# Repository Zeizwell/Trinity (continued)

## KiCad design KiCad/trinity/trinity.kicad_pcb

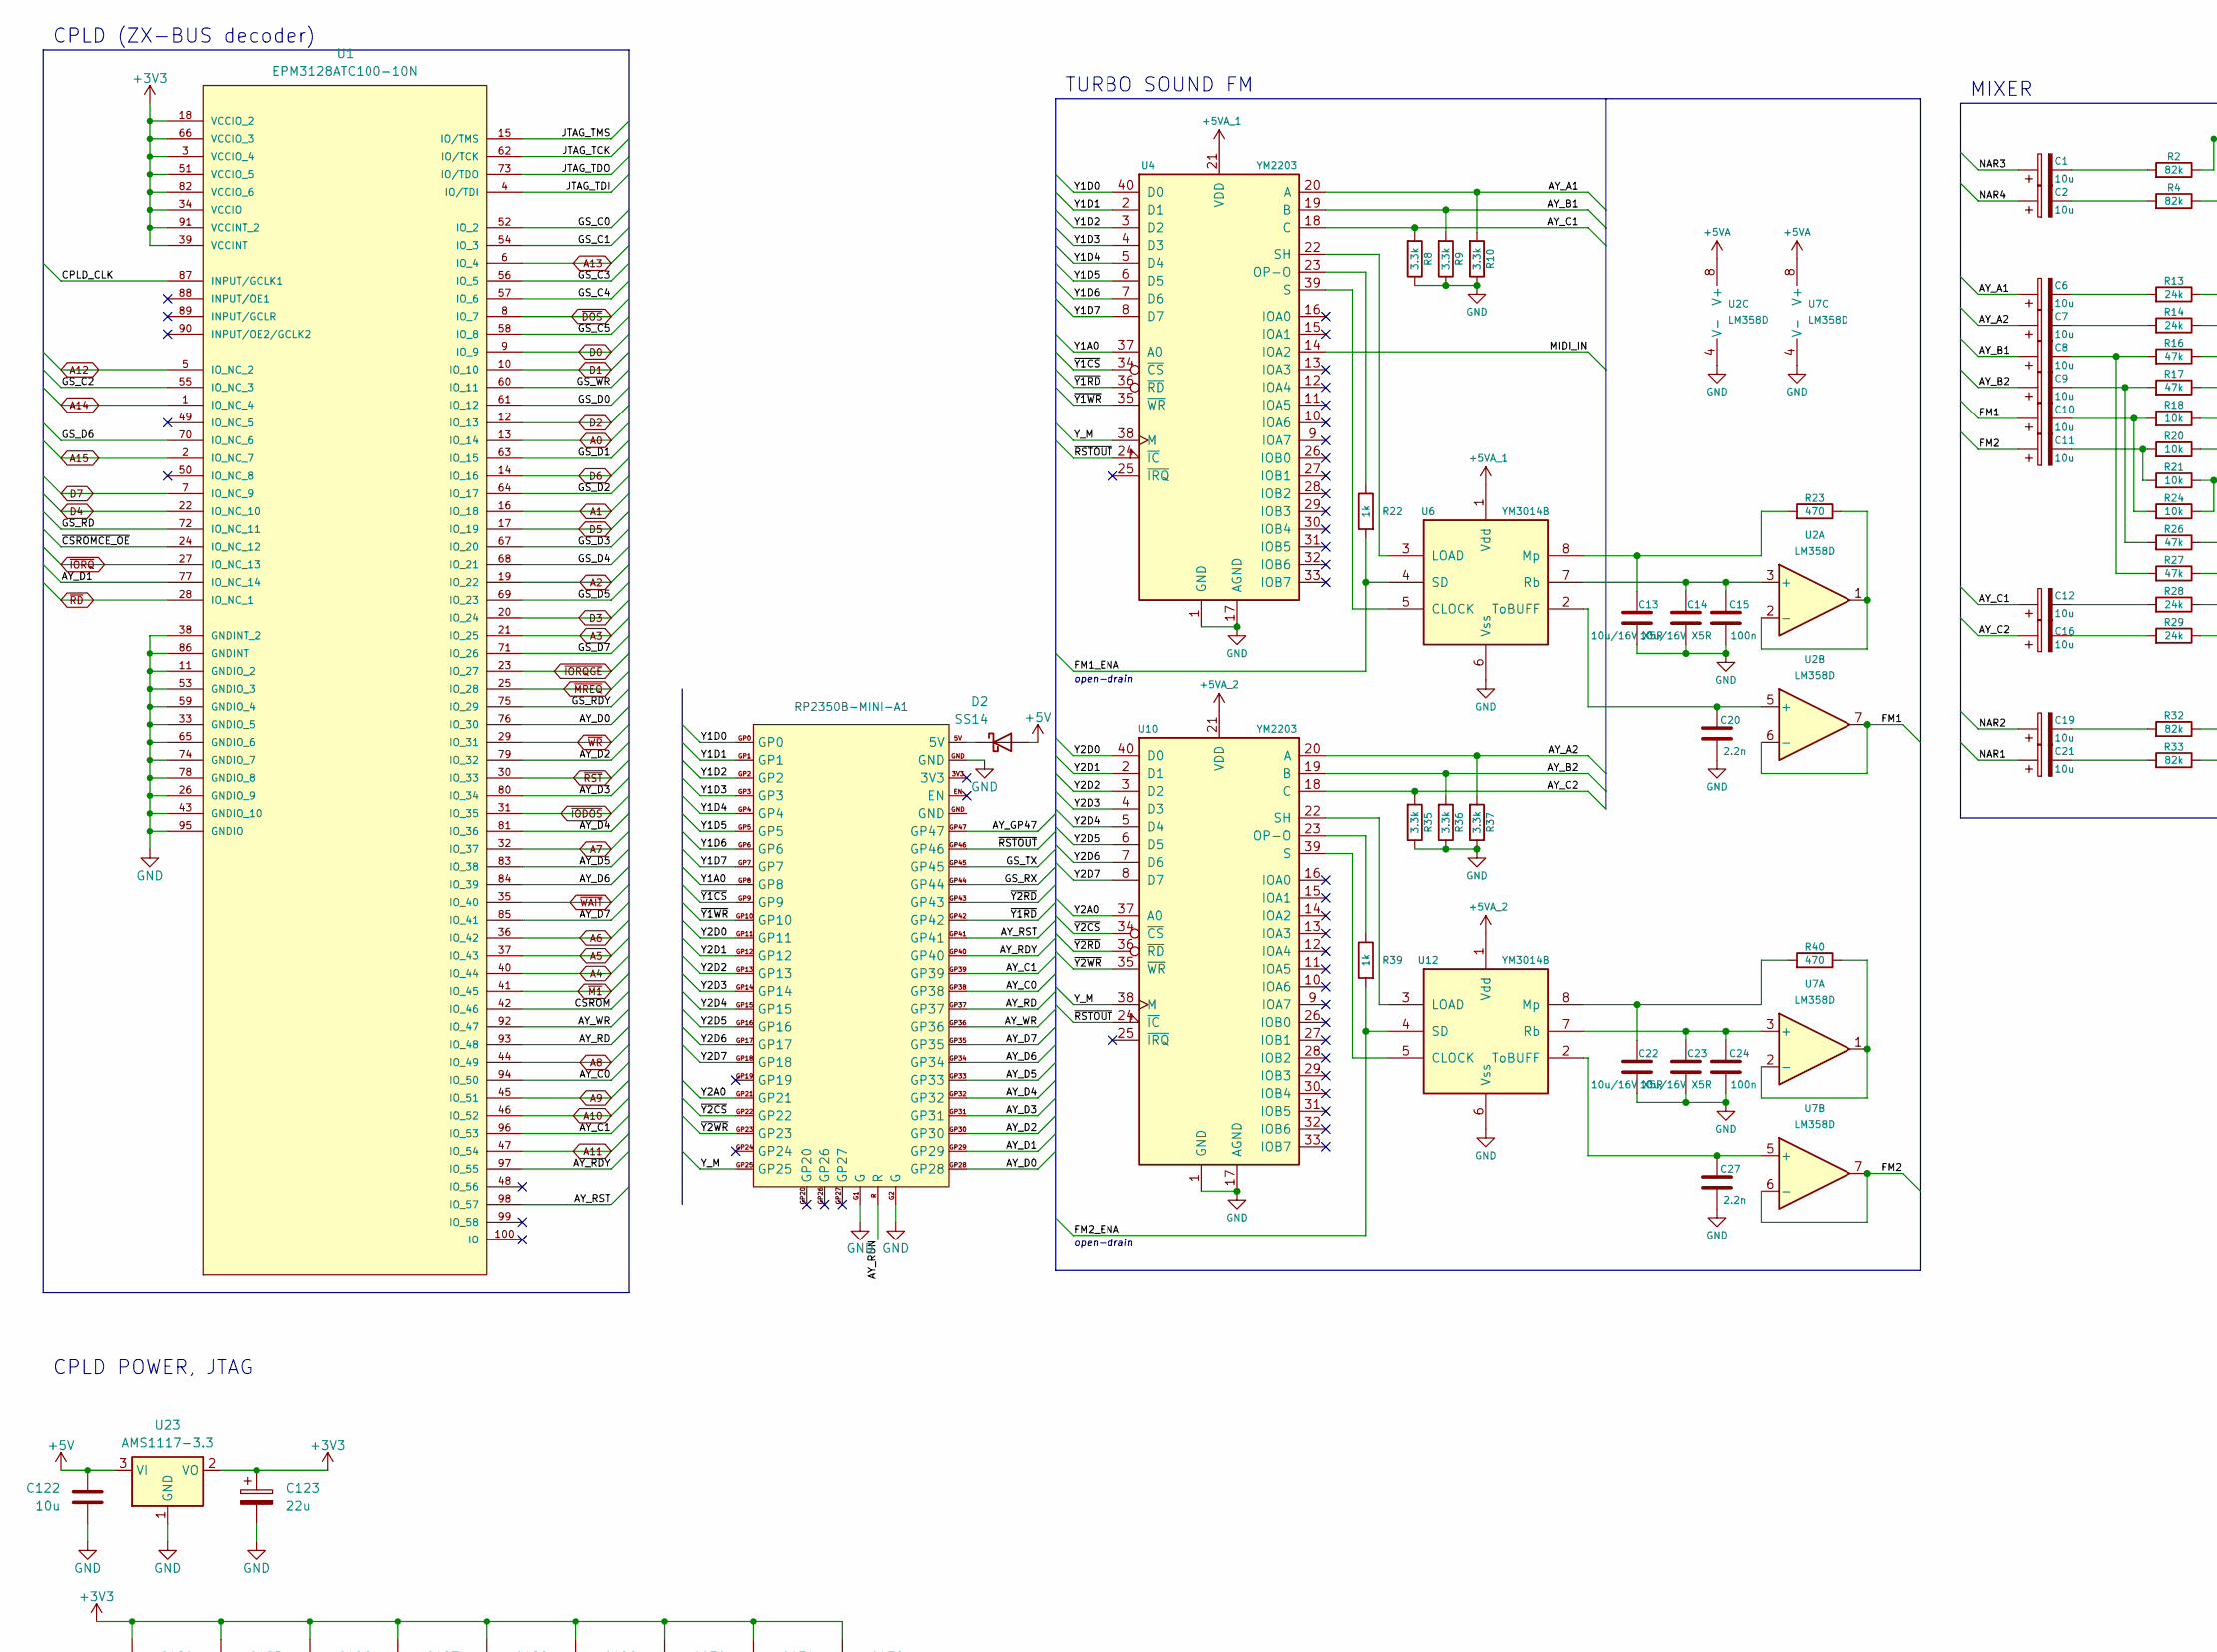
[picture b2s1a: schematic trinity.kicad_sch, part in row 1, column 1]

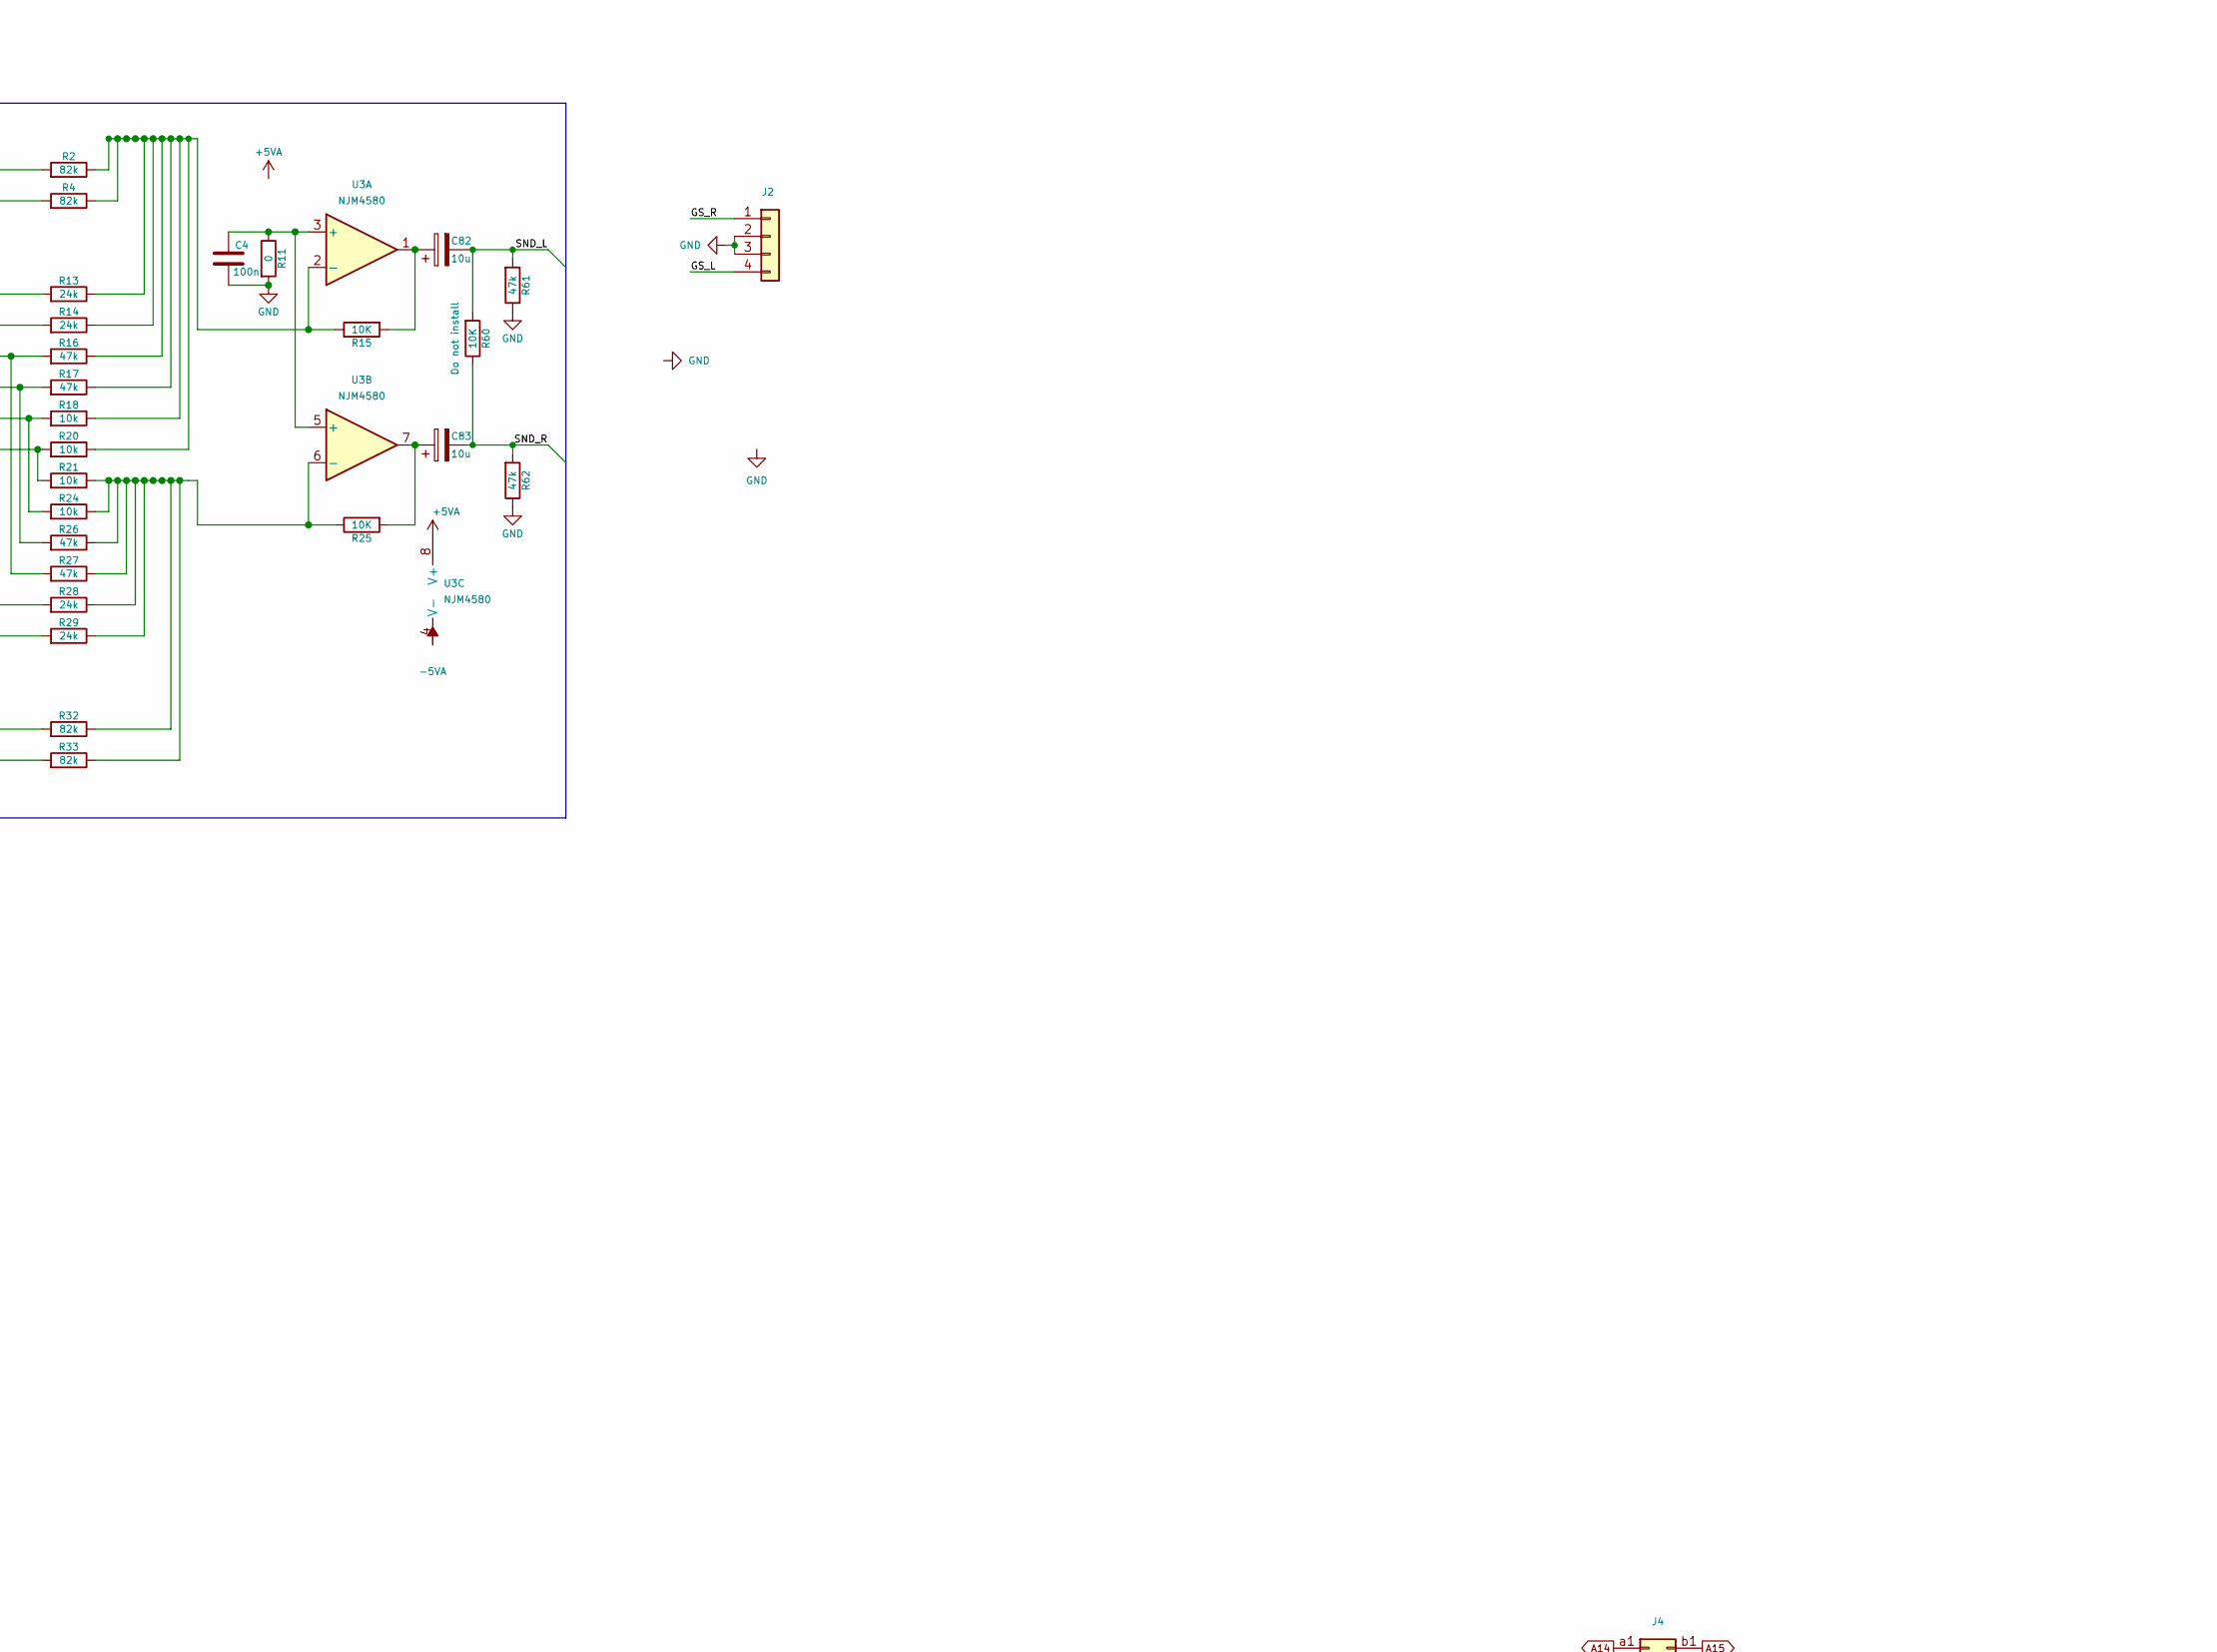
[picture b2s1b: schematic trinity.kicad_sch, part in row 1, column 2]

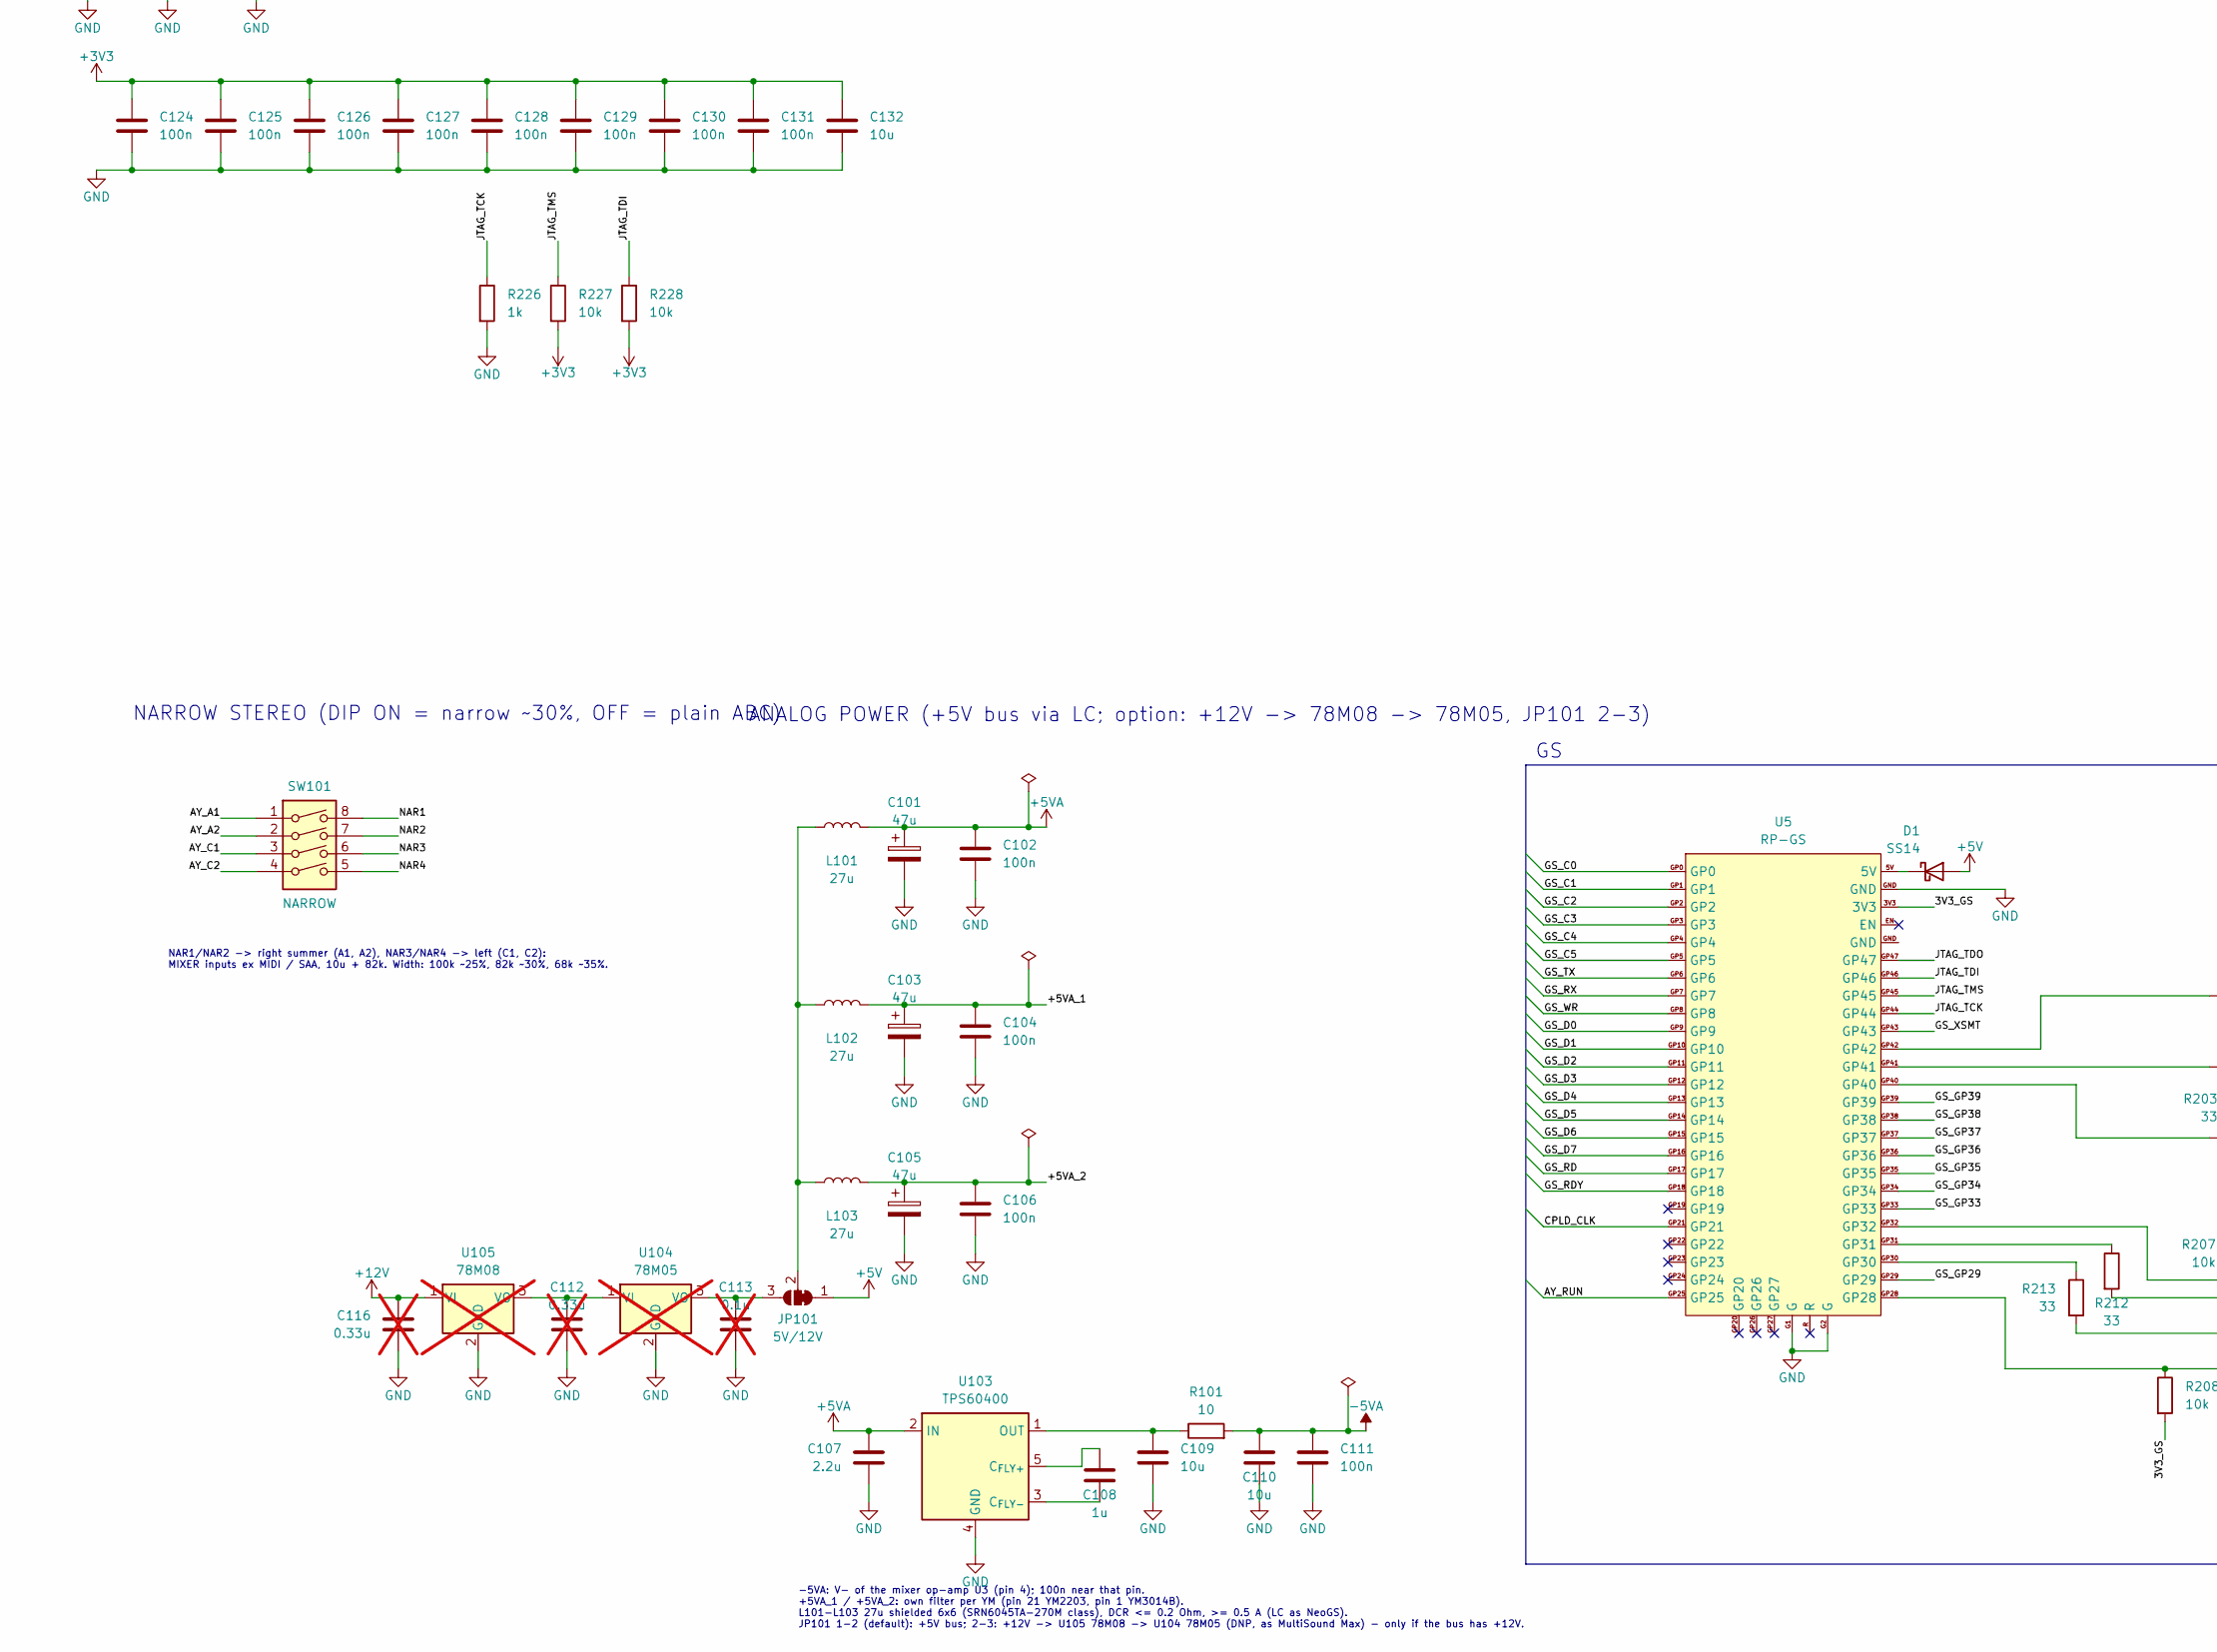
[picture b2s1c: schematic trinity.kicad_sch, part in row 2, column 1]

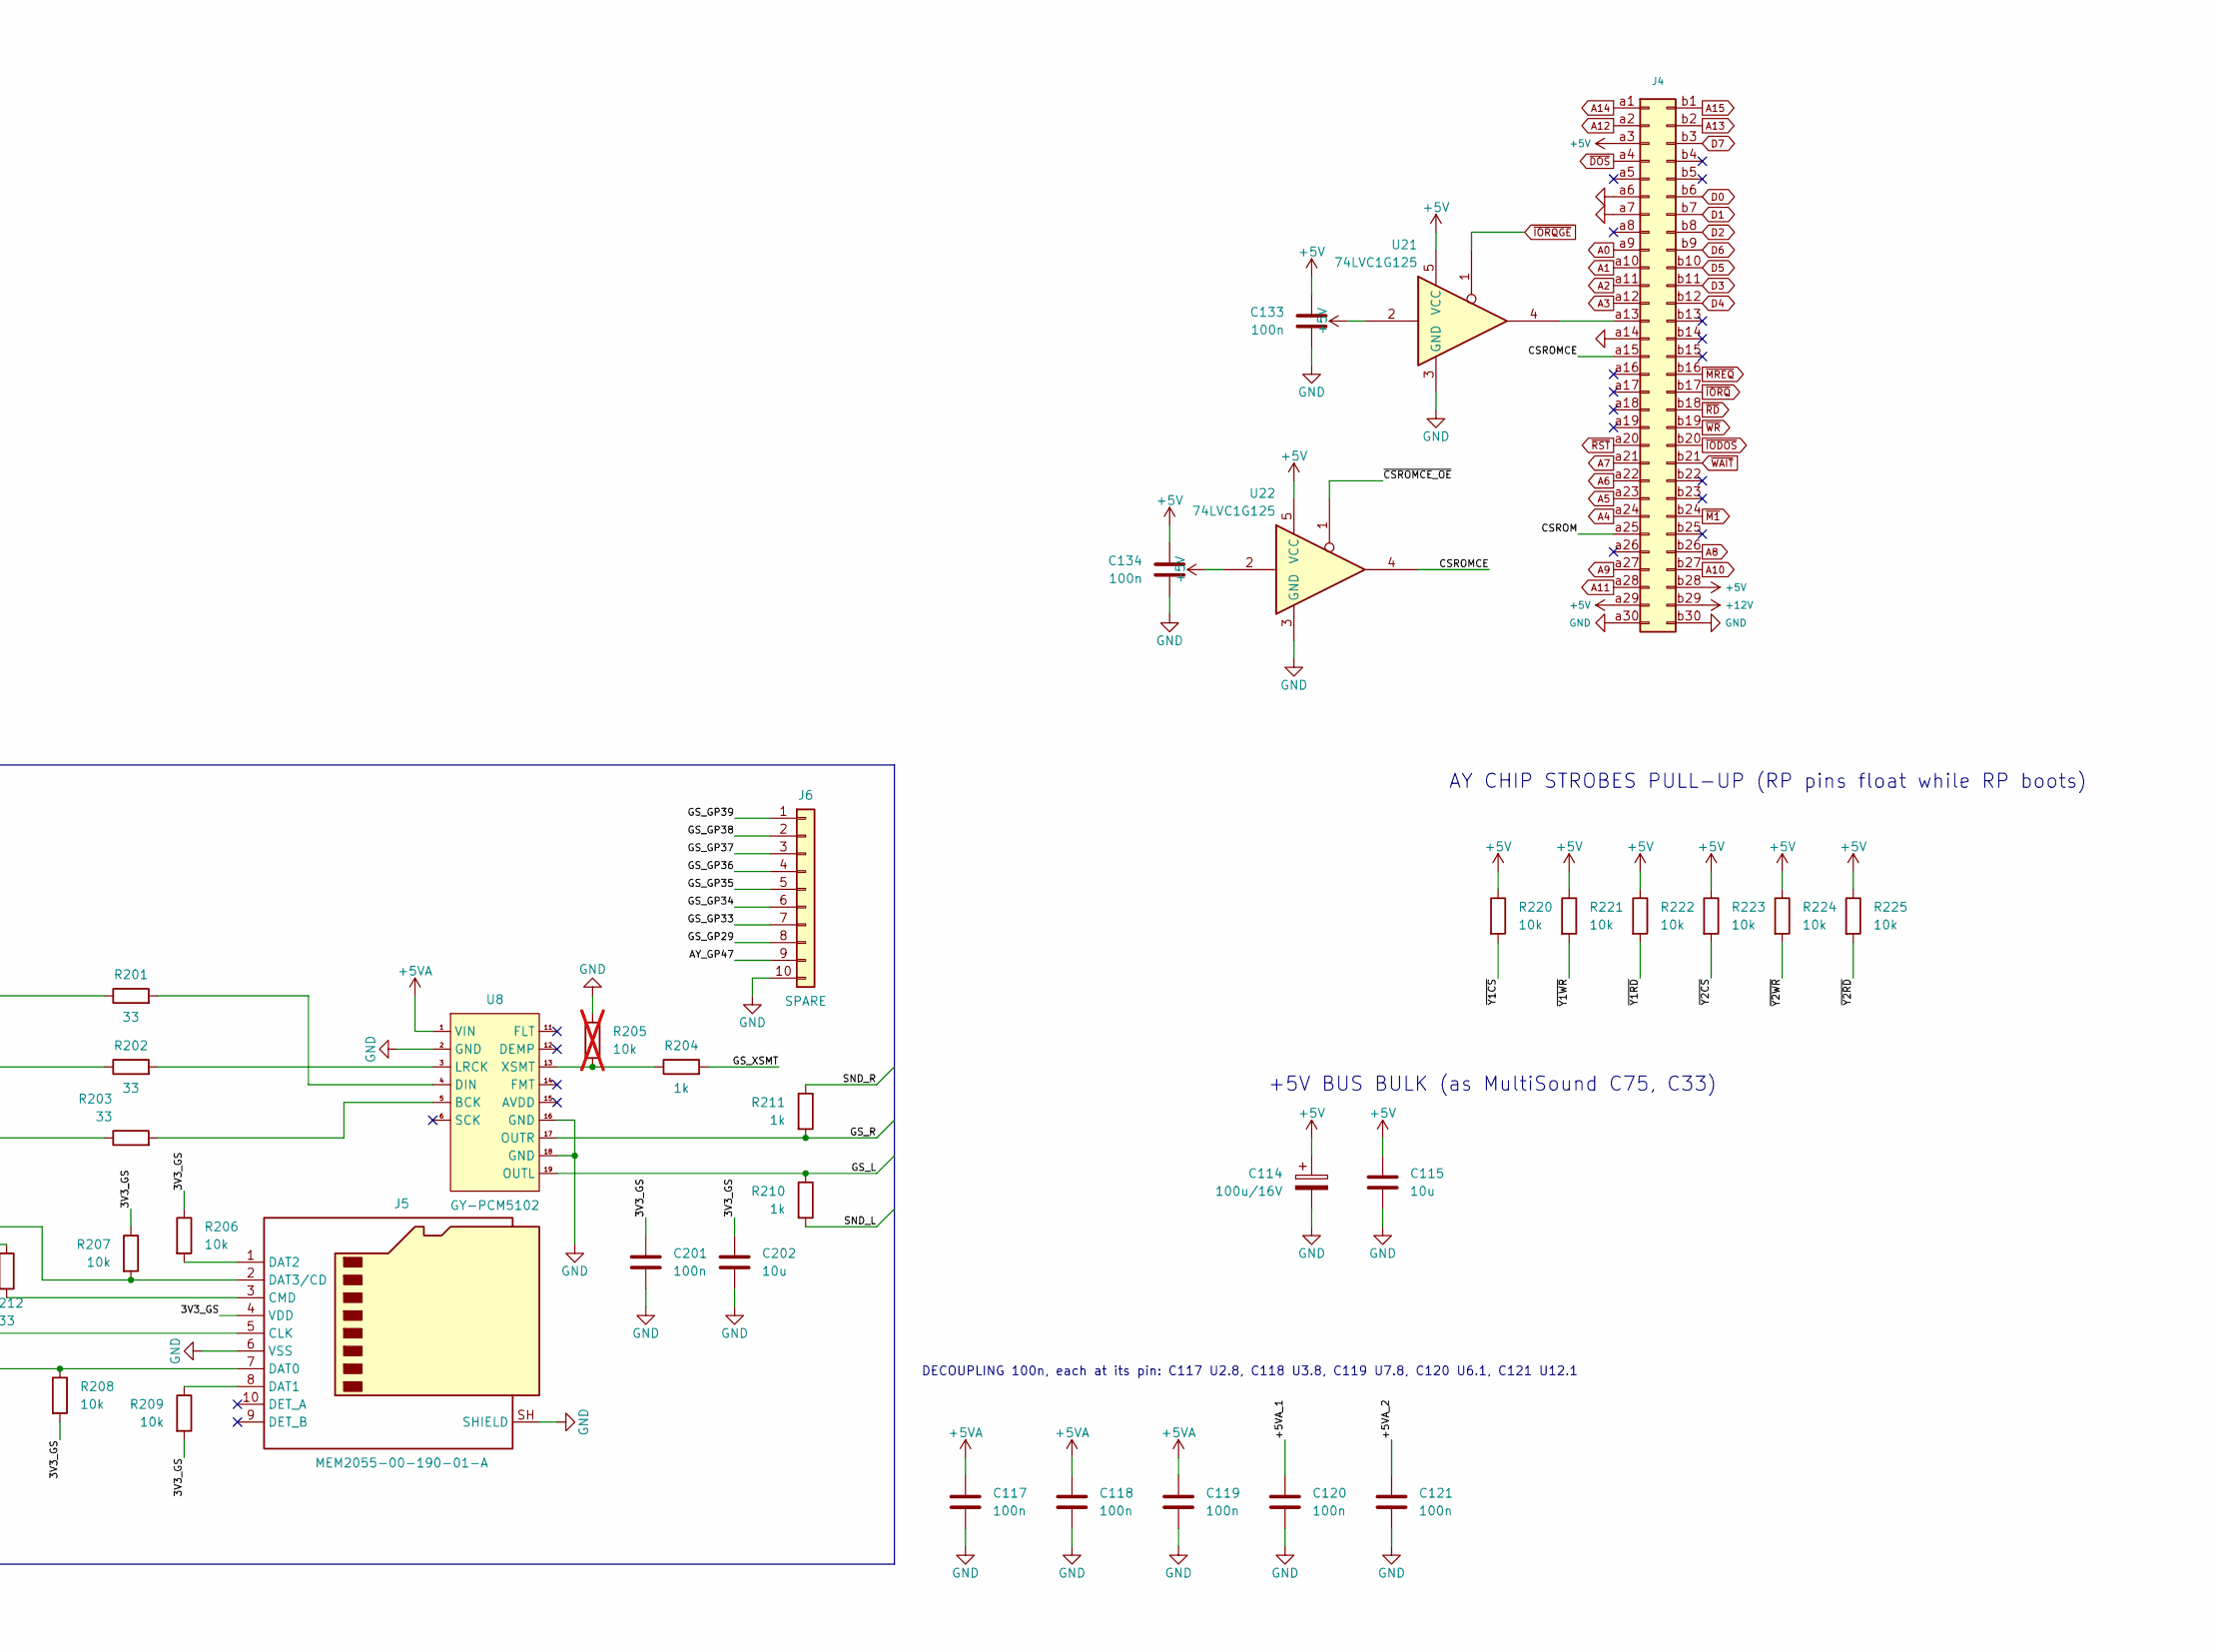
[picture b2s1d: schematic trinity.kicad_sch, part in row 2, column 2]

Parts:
C1, C2, C6, C7, C8, C9, C10, C11, C12, C16, C19, C21, C82, C83: 10u; CP_Elec_4x5.4
C4, C15, C24: 100n; C_0805_2012Metric_Pad1.18x1.45mm_HandSolder
C13, C14, C22, C23: 10u/16V X5R; C_1206_3216Metric
C20, C27: 2.2n; C_0805_2012Metric_Pad1.18x1.45mm_HandSolder
C101, C103, C105: 47u; CP_Elec_5x5.4
C102, C104, C106, C111, C117, C118, C119, C120, C121, C124, C125, C126, C127, C128, C129, C130, C131, C133, C134, C201: 100n; C_0603_1608Metric
C107: 2.2u; C_0603_1608Metric
C108: 1u; C_0603_1608Metric
C109, C110, C115, C122, C132, C202: 10u; C_0805_2012Metric
C112, C116: 0.33u; C_0603_1608Metric; not fitted
C113: 0.1u; C_0603_1608Metric; not fitted
C114: 100u/16V; CP_Elec_6.3x7.7
C123: 22u; CP_Elec_4x5.4
D1, D2: SS14; D_SMA
J2: Conn_01x04; PinHeader_1x04_P2.54mm_Vertical
J4: Conn_02x31_Row_Letter_First; ZX_NEMO_60_EDGE
J5: MEM2055-00-190-01-A; GCT-MEM2055-00-190-01-A
J6: SPARE; PinHeader_1x10_P2.54mm_Vertical
JP101: 5V/12V; SolderJumper-3_P1.3mm_Bridged12_RoundedPad1.0x1.5mm
L101, L102, L103: 27u; L_Bourns_SRN6045TA
R2, R4, R32, R33: 82k; R_0805_2012Metric_Pad1.20x1.40mm_HandSolder
R8, R9, R10, R35, R36, R37: 3.3k; R_0805_2012Metric_Pad1.20x1.40mm_HandSolder
R11: 0; R_0805_2012Metric_Pad1.20x1.40mm_HandSolder
R13, R14, R28, R29: 24k; R_0805_2012Metric_Pad1.20x1.40mm_HandSolder
R15, R25, R60: 10K; R_0805_2012Metric_Pad1.20x1.40mm_HandSolder
R16, R17, R26, R27, R61, R62: 47k; R_0805_2012Metric_Pad1.20x1.40mm_HandSolder
R18, R20, R21, R24: 10k; R_0805_2012Metric_Pad1.20x1.40mm_HandSolder
R22, R39: 1k; R_0805_2012Metric_Pad1.20x1.40mm_HandSolder
R23, R40: 470; R_0805_2012Metric_Pad1.20x1.40mm_HandSolder
R101: 10; R_0603_1608Metric
R201, R202, R203, R212, R213: 33; R_0603_1608Metric
R204, R210, R211, R226: 1k; R_0603_1608Metric
R205: 10k; R_0603_1608Metric; not fitted
R206, R207, R208, R209, R220, R221, R222, R223, R224, R225, R227, R228: 10k; R_0603_1608Metric
RP2350B-MINI-A1: rp2350b
SW101: NARROW; SW_DIP_SPSTx04_Slide_Omron_A6H-4101_W6.15mm_P1.27mm
U1: EPM3128ATC100-10N; QFP50P1600X1600X120-100N
U2, U7: LM358D; SOIC-8_3.9x4.9mm_P1.27mm
U3: NJM4580; SOIC-8_3.9x4.9mm_P1.27mm
U4, U10: YM2203; DIP-40_W15.24mm_Socket
U5: RP-GS; rp2350b
U6, U12: YM3014B; DIP-8_W7.62mm_Socket
U8: GY-PCM5102; PCM5102
U21, U22: 74LVC1G125; SOT-23-5
U23: AMS1117-3.3; SOT-223-3_TabPin2
U103: TPS60400; SOT-23-5
U104: 78M05; TO-252-2; not fitted
U105: 78M08; TO-252-2; not fitted

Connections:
+3V3: C123.1, C124.1, C125.1, C126.1, C127.1, C128.1, C129.1, C130.1, C131.1, C132.1, R227.2, R228.2, U1.3 (VCCIO_4), U1.18 (VCCIO_2), U1.34 (VCCIO), U1.39 (VCCINT), U1.51 (VCCIO_5), U1.66 (VCCIO_3), U1.82 (VCCIO_6), U1.91 (VCCINT_2), U23.2 (VO)
+5V: C114.1, C115.1, C122.1, C133.1, C134.1, D1.2 (A), D2.2 (A), J4.a3, J4.a29, J4.b28, JP101.1 (A), R220.1, R221.1, R222.1, R223.1, R224.1, R225.1, U21.2, U21.5 (VCC), U22.2, U22.5 (VCC), U23.3 (VI)
+12V: C116.1, J4.b29, U105.1 (VI)
/3V3_GS: C201.1, C202.1, J5.4 (VDD), R206.1, R207.1, R208.2, R209.2, U5.3V3
/AY_A1: C6.1, R10.2, SW101.1, U4.20 (A)
/AY_A2: C7.1, R37.2, SW101.2, U10.20 (A)
/AY_B1: C8.1, R9.2, U4.19 (B)
/AY_B2: C9.1, R36.2, U10.19 (B)
/AY_C0: RP2350B-MINI-A1.GP38, U1.94 (IO_50)
/AY_C1: C12.1, R8.2, RP2350B-MINI-A1.GP39, SW101.3, U1.96 (IO_53), U4.18 (C)
/AY_C2: C16.1, R35.2, SW101.4, U10.18 (C)
/AY_D0: RP2350B-MINI-A1.GP28, U1.76 (IO_30)
/AY_D1: RP2350B-MINI-A1.GP29, U1.77 (IO_NC_14)
/AY_D2: RP2350B-MINI-A1.GP30, U1.79 (IO_32)
/AY_D3: RP2350B-MINI-A1.GP31, U1.80 (IO_34)
/AY_D4: RP2350B-MINI-A1.GP32, U1.81 (IO_36)
/AY_D5: RP2350B-MINI-A1.GP33, U1.83 (IO_38)
/AY_D6: RP2350B-MINI-A1.GP34, U1.84 (IO_39)
/AY_D7: RP2350B-MINI-A1.GP35, U1.85 (IO_41)
/AY_GP47: J6.9, RP2350B-MINI-A1.GP47
/AY_RD: RP2350B-MINI-A1.GP37, U1.93 (IO_48)
/AY_RDY: RP2350B-MINI-A1.GP40, U1.97 (IO_55)
/AY_RST: RP2350B-MINI-A1.GP41, U1.98 (IO_57)
/AY_RUN: RP2350B-MINI-A1.R, U5.GP25
/AY_WR: RP2350B-MINI-A1.GP36, U1.92 (IO_47)
/CPLD_CLK: U1.87 (INPUT/GCLK1), U5.GP21
/CSROM: J4.a25, U1.42 (IO_46)
/CSROMCE: J4.a15, U22.4
/FM1: C10.1, U2.6 (-), U2.7
/FM1_ENA: R22.2, U6.4 (SD)
/FM2: C11.1, U7.6 (-), U7.7
/FM2_ENA: R39.2, U12.4 (SD)
/GS_C0: U1.52 (IO_2), U5.GP0
/GS_C1: U1.54 (IO_3), U5.GP1
/GS_C2: U1.55 (IO_NC_3), U5.GP2
/GS_C3: U1.56 (IO_5), U5.GP3
/GS_C4: U1.57 (IO_6), U5.GP4
/GS_C5: U1.58 (IO_8), U5.GP5
/GS_D0: U1.61 (IO_12), U5.GP9
/GS_D1: U1.63 (IO_15), U5.GP10
/GS_D2: U1.64 (IO_17), U5.GP11
/GS_D3: U1.67 (IO_20), U5.GP12
/GS_D4: U1.68 (IO_21), U5.GP13
/GS_D5: U1.69 (IO_23), U5.GP14
/GS_D6: U1.70 (IO_NC_6), U5.GP15
/GS_D7: U1.71 (IO_26), U5.GP16
/GS_GP29: J6.8, U5.GP29
/GS_GP33: J6.7, U5.GP33
/GS_GP34: J6.6, U5.GP34
/GS_GP35: J6.5, U5.GP35
/GS_GP36: J6.4, U5.GP36
/GS_GP37: J6.3, U5.GP37
/GS_GP38: J6.2, U5.GP38
/GS_GP39: J6.1, U5.GP39
/GS_L: J2.4, R210.1, U8.19 (OUTL)
/GS_R: J2.1, R211.2, U8.17 (OUTR)
/GS_RD: U1.72 (IO_NC_11), U5.GP17
/GS_RDY: U1.75 (IO_29), U5.GP18
/GS_RX: RP2350B-MINI-A1.GP44, U5.GP7
/GS_TX: RP2350B-MINI-A1.GP45, U5.GP6
/GS_WR: U1.60 (IO_11), U5.GP8
/GS_XSMT: R204.2, U5.GP43
/JTAG_TCK: R226.1, U1.62 (IO/TCK), U5.GP44
/JTAG_TDI: R228.1, U1.4 (IO/TDI), U5.GP46
/JTAG_TDO: U1.73 (IO/TDO), U5.GP47
/JTAG_TMS: R227.1, U1.15 (IO/TMS), U5.GP45
/MIDI_IN: U4.14 (IOA2)
/NAR1: C21.1, SW101.8
/NAR2: C19.1, SW101.7
/NAR3: C1.1, SW101.6
/NAR4: C2.1, SW101.5
/SND_L: C82.2, R60.2, R61.2, R210.2
/SND_R: C83.2, R60.1, R62.2, R211.1
/Y1A0: RP2350B-MINI-A1.GP8, U4.37 (A0)
/Y1D0: RP2350B-MINI-A1.GP0, U4.40 (D0)
/Y1D1: RP2350B-MINI-A1.GP1, U4.2 (D1)
/Y1D2: RP2350B-MINI-A1.GP2, U4.3 (D2)
/Y1D3: RP2350B-MINI-A1.GP3, U4.4 (D3)
/Y1D4: RP2350B-MINI-A1.GP4, U4.5 (D4)
/Y1D5: RP2350B-MINI-A1.GP5, U4.6 (D5)
/Y1D6: RP2350B-MINI-A1.GP6, U4.7 (D6)
/Y1D7: RP2350B-MINI-A1.GP7, U4.8 (D7)
/Y2A0: RP2350B-MINI-A1.GP21, U10.37 (A0)
/Y2D0: RP2350B-MINI-A1.GP11, U10.40 (D0)
/Y2D1: RP2350B-MINI-A1.GP12, U10.2 (D1)
/Y2D2: RP2350B-MINI-A1.GP13, U10.3 (D2)
/Y2D3: RP2350B-MINI-A1.GP14, U10.4 (D3)
/Y2D4: RP2350B-MINI-A1.GP15, U10.5 (D4)
/Y2D5: RP2350B-MINI-A1.GP16, U10.6 (D5)
/Y2D6: RP2350B-MINI-A1.GP17, U10.7 (D6)
/Y2D7: RP2350B-MINI-A1.GP18, U10.8 (D7)
/Y_M: RP2350B-MINI-A1.GP25, U4.38 (M), U10.38 (M)
/~CSROMCE_OE: U1.24 (IO_NC_12), U22.1
/~RSTOUT: RP2350B-MINI-A1.GP46, U4.24 (~IC), U10.24 (~IC)
/~Y1CS: R220.2, RP2350B-MINI-A1.GP9, U4.34 (~CS)
/~Y1RD: R222.2, RP2350B-MINI-A1.GP42, U4.36 (~RD)
/~Y1WR: R221.2, RP2350B-MINI-A1.GP10, U4.35 (~WR)
/~Y2CS: R223.2, RP2350B-MINI-A1.GP22, U10.34 (~CS)
/~Y2RD: R225.2, RP2350B-MINI-A1.GP43, U10.36 (~RD)
/~Y2WR: R224.2, RP2350B-MINI-A1.GP23, U10.35 (~WR)
A0: J4.a9, U1.13 (IO_14)
A1: J4.a10, U1.16 (IO_18)
A2: J4.a11, U1.19 (IO_22)
A3: J4.a12, U1.21 (IO_25)
A4: J4.a24, U1.40 (IO_44)
A5: J4.a23, U1.37 (IO_43)
A6: J4.a22, U1.36 (IO_42)
A7: J4.a21, U1.32 (IO_37)
A8: J4.b26, U1.44 (IO_49)
A9: J4.a27, U1.45 (IO_51)
A10: J4.b27, U1.46 (IO_52)
A11: J4.a28, U1.47 (IO_54)
A12: J4.a2, U1.5 (IO_NC_2)
A13: J4.b2, U1.6 (IO_4)
A14: J4.a1, U1.1 (IO_NC_4)
A15: J4.b1, U1.2 (IO_NC_7)
D0: J4.b6, U1.9 (IO_9)
D1: J4.b7, U1.10 (IO_10)
D2: J4.b8, U1.12 (IO_13)
D3: J4.b11, U1.20 (IO_24)
D4: J4.b12, U1.22 (IO_NC_10)
D5: J4.b10, U1.17 (IO_19)
D6: J4.b9, U1.14 (IO_16)
D7: J4.b3, U1.7 (IO_NC_9)
GND: C4.1, C13.2, C14.2, C15.2, C20.2, C22.2, C23.2, C24.2, C27.2, C101.2, C102.2, C103.2, C104.2, C105.2, C106.2, C107.2, C109.2, C110.2, C111.2, C112.2, C113.2, C114.2, C115.2, C116.2, C117.2, C118.2, C119.2, C120.2, C121.2, C122.2, C123.2, C124.2, C125.2, C126.2, C127.2, C128.2, C129.2, C130.2, C131.2, C132.2, C133.2, C134.2, C201.2, C202.2, J2.2, J2.3, J4.a6, J4.a7, J4.a14, J4.a30, J4.b30, J5.6 (VSS), J5.SH (SHIELD), J6.10, R8.1, R9.1, R10.1, R11.2, R35.1, R36.1, R37.1, R61.1, R62.1, R205.1, R226.2, RP2350B-MINI-A1.G1 (G), RP2350B-MINI-A1.G2 (G), RP2350B-MINI-A1.GND, U1.11 (GNDIO_2), U1.26 (GNDIO_9), U1.33 (GNDIO_5), U1.38 (GNDINT_2), U1.43 (GNDIO_10), U1.53 (GNDIO_3), U1.59 (GNDIO_4), U1.65 (GNDIO_6), U1.74 (GNDIO_7), U1.78 (GNDIO_8), U1.86 (GNDINT), U1.95 (GNDIO), U2.4 (V-), U4.1 (GND), U4.17 (AGND), U5.G1 (G), U5.G2 (G), U5.GND, U6.6 (Vss), U7.4 (V-), U8.2 (GND), U8.16 (GND), U8.18 (GND), U10.1 (GND), U10.17 (AGND), U12.6 (Vss), U21.3 (GND), U22.3 (GND), U23.1 (GND), U103.4 (GND), U104.2 (GND), U105.2 (GND)
unnamed: C1.2, R2.2
unnamed: C2.2, R4.2
unnamed: C6.2, R13.2
unnamed: C7.2, R14.2
unnamed: C8.2, R16.2, R27.2
unnamed: C9.2, R17.2, R26.2
unnamed: C10.2, R18.2, R24.2
unnamed: C11.2, R20.2, R21.2
unnamed: C12.2, R28.2
unnamed: C16.2, R29.2
unnamed: C19.2, R32.2
unnamed: C21.2, R33.2
unnamed: C82.1, R15.2, U3.1
unnamed: C83.1, R25.2, U3.7
unnamed: D1.1 (K), U5.5V
unnamed: D2.1 (K), RP2350B-MINI-A1.5V
unnamed: J4.a13, U21.4
unnamed: J5.5 (CLK), R213.2
unnamed: J5.3 (CMD), R212.2
unnamed: J5.7 (DAT0), R208.1, U5.GP28
unnamed: J5.8 (DAT1), R209.1
unnamed: J5.1 (DAT2), R206.2
unnamed: J5.2 (DAT3/CD), R207.2, U5.GP32
unnamed: C113.1, JP101.3 (B), U104.3 (VO)
unnamed: JP101.2 (C), L101.1, L102.1, L103.1
unnamed: R201.1, U5.GP42
unnamed: R202.1, U5.GP41
unnamed: R203.1, U5.GP40
unnamed: R212.1, U5.GP31
unnamed: R213.1, U5.GP30
unnamed: C14.1, C15.1, U2.3 (+), U6.7 (Rb)
unnamed: R23.1, U2.1, U2.2 (-)
unnamed: C20.1, U2.5 (+), U6.2 (ToBUFF)
unnamed: C4.2, R11.1, U3.3 (+), U3.5 (+)
unnamed: R2.1, R4.1, R13.1, R14.1, R15.1, R16.1, R17.1, R18.1, R20.1, U3.2 (-)
unnamed: R21.1, R24.1, R25.1, R26.1, R27.1, R28.1, R29.1, R32.1, R33.1, U3.6 (-)
unnamed: R22.1, U4.23 (OP-O)
unnamed: U4.39 (S), U6.5 (CLOCK)
unnamed: U4.22 (SH), U6.3 (LOAD)
unnamed: C13.1, R23.2, U6.8 (Mp)
unnamed: R40.1, U7.1, U7.2 (-)
unnamed: R203.2, U8.5 (BCK)
unnamed: R201.2, U8.4 (DIN)
unnamed: R202.2, U8.3 (LRCK)
unnamed: R204.1, R205.2, U8.13 (XSMT)
unnamed: R39.1, U10.23 (OP-O)
unnamed: U10.39 (S), U12.5 (CLOCK)
unnamed: U10.22 (SH), U12.3 (LOAD)
unnamed: C22.1, R40.2, U12.8 (Mp)
unnamed: C23.1, C24.1, U7.3 (+), U12.7 (Rb)
unnamed: C27.1, U7.5 (+), U12.2 (ToBUFF)
unnamed: C108.1, U103.5 (C_{FLY+})
unnamed: C108.2, U103.3 (C_{FLY-})
unnamed: C109.1, R101.1, U103.1 (OUT)
unnamed: C112.1, U104.1 (VI), U105.3 (VO)
~DOS: J4.a4, U1.8 (IO_7)
~IODOS: J4.b20, U1.31 (IO_35)
~IORQGE: U1.23 (IO_27), U21.1
~IORQ: J4.b17, U1.27 (IO_NC_13)
~M1: J4.b24, U1.41 (IO_45)
~MREQ: J4.b16, U1.25 (IO_28)
~RD: J4.b18, U1.28 (IO_NC_1)
~RST: J4.a20, U1.30 (IO_33)
~WAIT: J4.b21, U1.35 (IO_40)
~WR: J4.b19, U1.29 (IO_31)

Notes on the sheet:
open-drain
MIXER
TURBO SOUND FM
-5VA: V- of the mixer op-amp U3 (pin 4); 100n near that pin. +5VA_1 / +5VA_2: own filter per YM (pin 21 YM2203, pin 1 YM3014B). L101-L103 27u shielded 6x6 (SRN6045TA-270M class), DCR <= 0.2 Ohm, >= 0.5 A (LC as NeoGS). JP101 1-2 (default): +5V bus; 2-3: +12V -> U105 78M08 -> U104 78M05 (DNP, as Mul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
NAR1/NAR2 -> right summer (A1, A2), NAR3/NAR4 -> left (C1, C2): MIXER inputs ex MIDI / SAA, 10u + 82k. Width: 100k ~25%, 82k ~30%, 68k ~35%.
ANALOG POWER (+5V bus via LC; option: +12V -> 78M08 -> 78M05, JP101 2-3)
NARROW STEREO (DIP ON = narrow ~30%, OFF = plain ABC)
AY CHIP STROBES PULL-UP (RP pins float while RP boots)
+5V BUS BULK (as MultiSound C75, C33)
DECOUPLING 100n, each at its pin: C117 U2.8, C118 U3.8, C119 U7.8, C120 U6.1, C121 U12.1
CPLD POWER, JTAG
CPLD (ZX-BUS decoder)

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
